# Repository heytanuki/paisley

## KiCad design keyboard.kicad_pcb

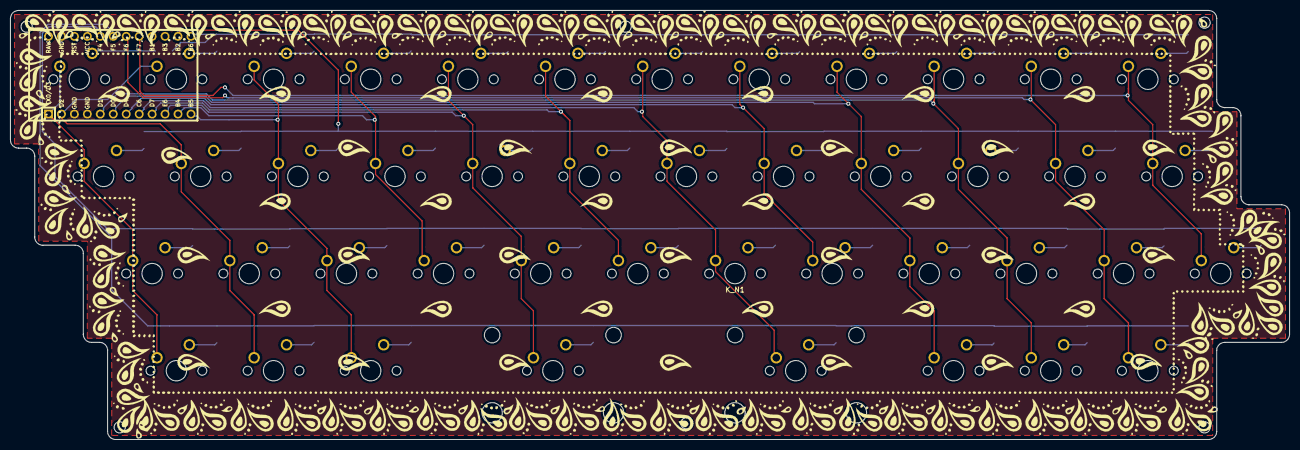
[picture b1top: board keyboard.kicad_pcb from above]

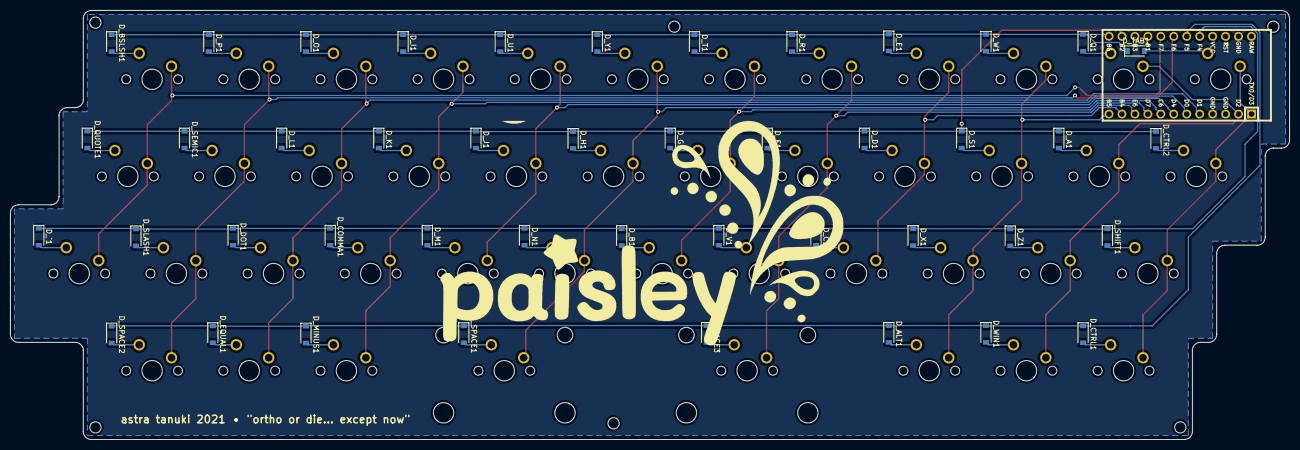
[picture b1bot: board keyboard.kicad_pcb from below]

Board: 2 copper layers, 250.8 x 84.1 mm, 89 parts (44 on the bottom side), 61 nets.

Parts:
D_A1: D; D_SOD-123
D_ALT1: D; D_SOD-123
D_B1: D; D_SOD-123
D_BSLSH1: D; D_SOD-123
D_C1: D; D_SOD-123
D_COMMA1: D; D_SOD-123
D_CTRL1, D_CTRL2: D; D_SOD-123
D_D1: D; D_SOD-123
D_DOT1: D; D_SOD-123
D_E1: D; D_SOD-123
D_EQUAL1: D; D_SOD-123
D_F1: D; D_SOD-123
D_G1: D; D_SOD-123
D_H1: D; D_SOD-123
D_I1: D; D_SOD-123
D_J1: D; D_SOD-123
D_K1: D; D_SOD-123
D_L1: D; D_SOD-123
D_M1: D; D_SOD-123
D_MINUS1: D; D_SOD-123
D_N1: D; D_SOD-123
D_O1: D; D_SOD-123
D_P1: D; D_SOD-123
D_Q1: D; D_SOD-123
D_QUOTE1: D; D_SOD-123
D_R1: D; D_SOD-123
D_S1: D; D_SOD-123
D_SEMIC1: D; D_SOD-123
D_SHIFT1: D; D_SOD-123
D_SLASH1: D; D_SOD-123
D_SPACE1, D_SPACE2, D_SPACE3: D; D_SOD-123
D_T1: D; D_SOD-123
D_TAB1: D; D_SOD-123
D_U1: D; D_SOD-123
D_V1: D; D_SOD-123
D_W1: D; D_SOD-123
D_WIN1: D; D_SOD-123
D_X1: D; D_SOD-123
D_Y1: D; D_SOD-123
D_Z1: D; D_SOD-123
D_`1: D; D_SOD-123
K_A1: KEYSW; MXOnly-1U-NoLED
K_ALT1: KEYSW; MXOnly-1U-NoLED
K_B1: KEYSW; MXOnly-1U-NoLED
K_BSLSH1: KEYSW; MXOnly-1U-NoLED
K_C1: KEYSW; MXOnly-1U-NoLED
K_COMMA1: KEYSW; MXOnly-1U-NoLED
K_CTRL1, K_CTRL2: KEYSW; MXOnly-1U-NoLED
K_D1: KEYSW; MXOnly-1U-NoLED
K_DOT1: KEYSW; MXOnly-1U-NoLED
K_E1: KEYSW; MXOnly-1U-NoLED
K_EQUAL1: KEYSW; MXOnly-1U-NoLED
K_F1: KEYSW; MXOnly-1U-NoLED
K_G1: KEYSW; MXOnly-1U-NoLED
K_H1: KEYSW; MXOnly-1U-NoLED
K_I1: KEYSW; MXOnly-1U-NoLED
K_J1: KEYSW; MXOnly-1U-NoLED
K_K1: KEYSW; MXOnly-1U-NoLED
K_L1: KEYSW; MXOnly-1U-NoLED
K_M1: KEYSW; MXOnly-1U-NoLED
K_MINUS1: KEYSW; MXOnly-1U-NoLED
K_N1: KEYSW; MXOnly-1U-NoLED
K_O1: KEYSW; MXOnly-1U-NoLED
K_P1: KEYSW; MXOnly-1U-NoLED
K_Q1: KEYSW; MXOnly-1U-NoLED
K_QUOTE1: KEYSW; MXOnly-1U-NoLED
K_R1: KEYSW; MXOnly-1U-NoLED
K_S1: KEYSW; MXOnly-1U-NoLED
K_SEMIC1: KEYSW; MXOnly-1U-NoLED
K_SHIFT1: KEYSW; MXOnly-1U-NoLED
K_SLASH1: KEYSW; MXOnly-1U-NoLED
K_SPACE1: KEYSW; MXOnly-2.25U-NoLED
K_SPACE2: KEYSW; MXOnly-1U-NoLED
K_SPACE3: KEYSW; MXOnly-2.75U-NoLED
K_T1: KEYSW; MXOnly-1U-NoLED
K_TAB1: KEYSW; MXOnly-1U-NoLED
K_U1: KEYSW; MXOnly-1U-NoLED
K_V1: KEYSW; MXOnly-1U-NoLED
K_W1: KEYSW; MXOnly-1U-NoLED
K_WIN1: KEYSW; MXOnly-1U-NoLED
K_X1: KEYSW; MXOnly-1U-NoLED
K_Y1: KEYSW; MXOnly-1U-NoLED
K_Z1: KEYSW; MXOnly-1U-NoLED
K_`1: KEYSW; MXOnly-1U-NoLED
U1: ProMicro; ArduinoProMicro

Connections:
GND: U1.3, U1.4, U1.23
unnamed: D_A1.2, K_A1.2
unnamed: D_ALT1.2, K_ALT1.2
unnamed: D_B1.2, K_B1.2
unnamed: D_BSLSH1.2, K_BSLSH1.2
unnamed: D_C1.2, K_C1.2
unnamed: D_COMMA1.2, K_COMMA1.2
unnamed: D_CTRL1.2, K_CTRL1.2
unnamed: D_CTRL2.2, K_CTRL2.2
unnamed: D_D1.2, K_D1.2
unnamed: D_DOT1.2, K_DOT1.2
unnamed: D_E1.2, K_E1.2
unnamed: D_EQUAL1.2, K_EQUAL1.2
unnamed: D_F1.2, K_F1.2
unnamed: D_G1.2, K_G1.2
unnamed: D_H1.2, K_H1.2
unnamed: D_I1.2, K_I1.2
unnamed: D_J1.2, K_J1.2
unnamed: D_K1.2, K_K1.2
unnamed: D_L1.2, K_L1.2
unnamed: D_M1.2, K_M1.2
unnamed: D_MINUS1.2, K_MINUS1.2
unnamed: D_N1.2, K_N1.2
unnamed: D_O1.2, K_O1.2
unnamed: D_P1.2, K_P1.2
unnamed: D_Q1.2, K_Q1.2
unnamed: D_QUOTE1.2, K_QUOTE1.2
unnamed: D_R1.2, K_R1.2
unnamed: D_S1.2, K_S1.2
unnamed: D_SEMIC1.2, K_SEMIC1.2
unnamed: D_SHIFT1.2, K_SHIFT1.2
unnamed: D_SLASH1.2, K_SLASH1.2
unnamed: D_SPACE1.2, K_SPACE1.2
unnamed: D_SPACE2.2, K_SPACE2.2
unnamed: D_SPACE3.2, K_SPACE3.2
unnamed: D_T1.2, K_T1.2
unnamed: D_TAB1.2, K_TAB1.2
unnamed: D_U1.2, K_U1.2
unnamed: D_V1.2, K_V1.2
unnamed: D_W1.2, K_W1.2
unnamed: D_WIN1.2, K_WIN1.2
unnamed: D_X1.2, K_X1.2
unnamed: D_Y1.2, K_Y1.2
unnamed: D_Z1.2, K_Z1.2
unnamed: D_`1.2, K_`1.2
col0: K_CTRL1.1, K_CTRL2.1, K_SHIFT1.1, K_TAB1.1, U1.1
col1: K_A1.1, K_Q1.1, K_WIN1.1, K_Z1.1, U1.2
col2: K_ALT1.1, K_S1.1, K_W1.1, K_X1.1, U1.12
col3: K_C1.1, K_D1.1, K_E1.1, U1.11
col4: K_F1.1, K_R1.1, K_SPACE3.1, K_V1.1, U1.10
col5: K_B1.1, K_G1.1, K_T1.1, U1.9
col6: K_H1.1, K_N1.1, K_SPACE1.1, K_Y1.1, U1.8
col7: K_J1.1, K_M1.1, K_U1.1, U1.7
col8: K_COMMA1.1, K_I1.1, K_K1.1, K_MINUS1.1, U1.6
col9: K_DOT1.1, K_EQUAL1.1, K_L1.1, K_O1.1, U1.5
col10: K_P1.1, K_SEMIC1.1, K_SLASH1.1, K_SPACE2.1, U1.18
col11: K_BSLSH1.1, K_QUOTE1.1, K_`1.1, U1.17
row0: D_BSLSH1.1, D_E1.1, D_I1.1, D_O1.1, D_P1.1, D_Q1.1, D_R1.1, D_T1.1, D_TAB1.1, D_U1.1, D_W1.1, D_Y1.1, U1.13
row1: D_A1.1, D_CTRL2.1, D_D1.1, D_F1.1, D_G1.1, D_H1.1, D_J1.1, D_K1.1, D_L1.1, D_QUOTE1.1, D_S1.1, D_SEMIC1.1, U1.14
row2: D_B1.1, D_C1.1, D_COMMA1.1, D_DOT1.1, D_M1.1, D_N1.1, D_SHIFT1.1, D_SLASH1.1, D_V1.1, D_X1.1, D_Z1.1, D_`1.1, U1.20
row3: D_ALT1.1, D_CTRL1.1, D_EQUAL1.1, D_MINUS1.1, D_SPACE1.1, D_SPACE2.1, D_SPACE3.1, D_WIN1.1, U1.19
